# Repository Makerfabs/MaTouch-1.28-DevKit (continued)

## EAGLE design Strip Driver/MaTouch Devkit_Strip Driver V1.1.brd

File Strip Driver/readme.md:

# MaTouch1.28" DevKit Strip Driver

```c++
/*
Library version:
Arduino IDE 2.3.4
esp32 V3.1.1
GFX Library for Arduino v1.5.4
lvgl v8.3.11
RTClib v2.1.4
Adafruit BusIO v1.16.2
ESP32Time v2.0.6

Tools:
USB CDC On Boot: Enabled
Flash size: 16MB(128Mb)
Partition Schrme: 16M Flash(3MB APP/9.9MB FATFS)
PSRAM: OPI PSRAM
*/
```
## Introduce

1.[How to use?](https://wiki.makerfabs.com/Matouch%201.28%20DevKit.html#23-rgb-led-strip-driver)

2.[How to upload code?](https://wiki.makerfabs.com/Matouch%201.28%20DevKit.html#33-rgb-led-strip-driver)

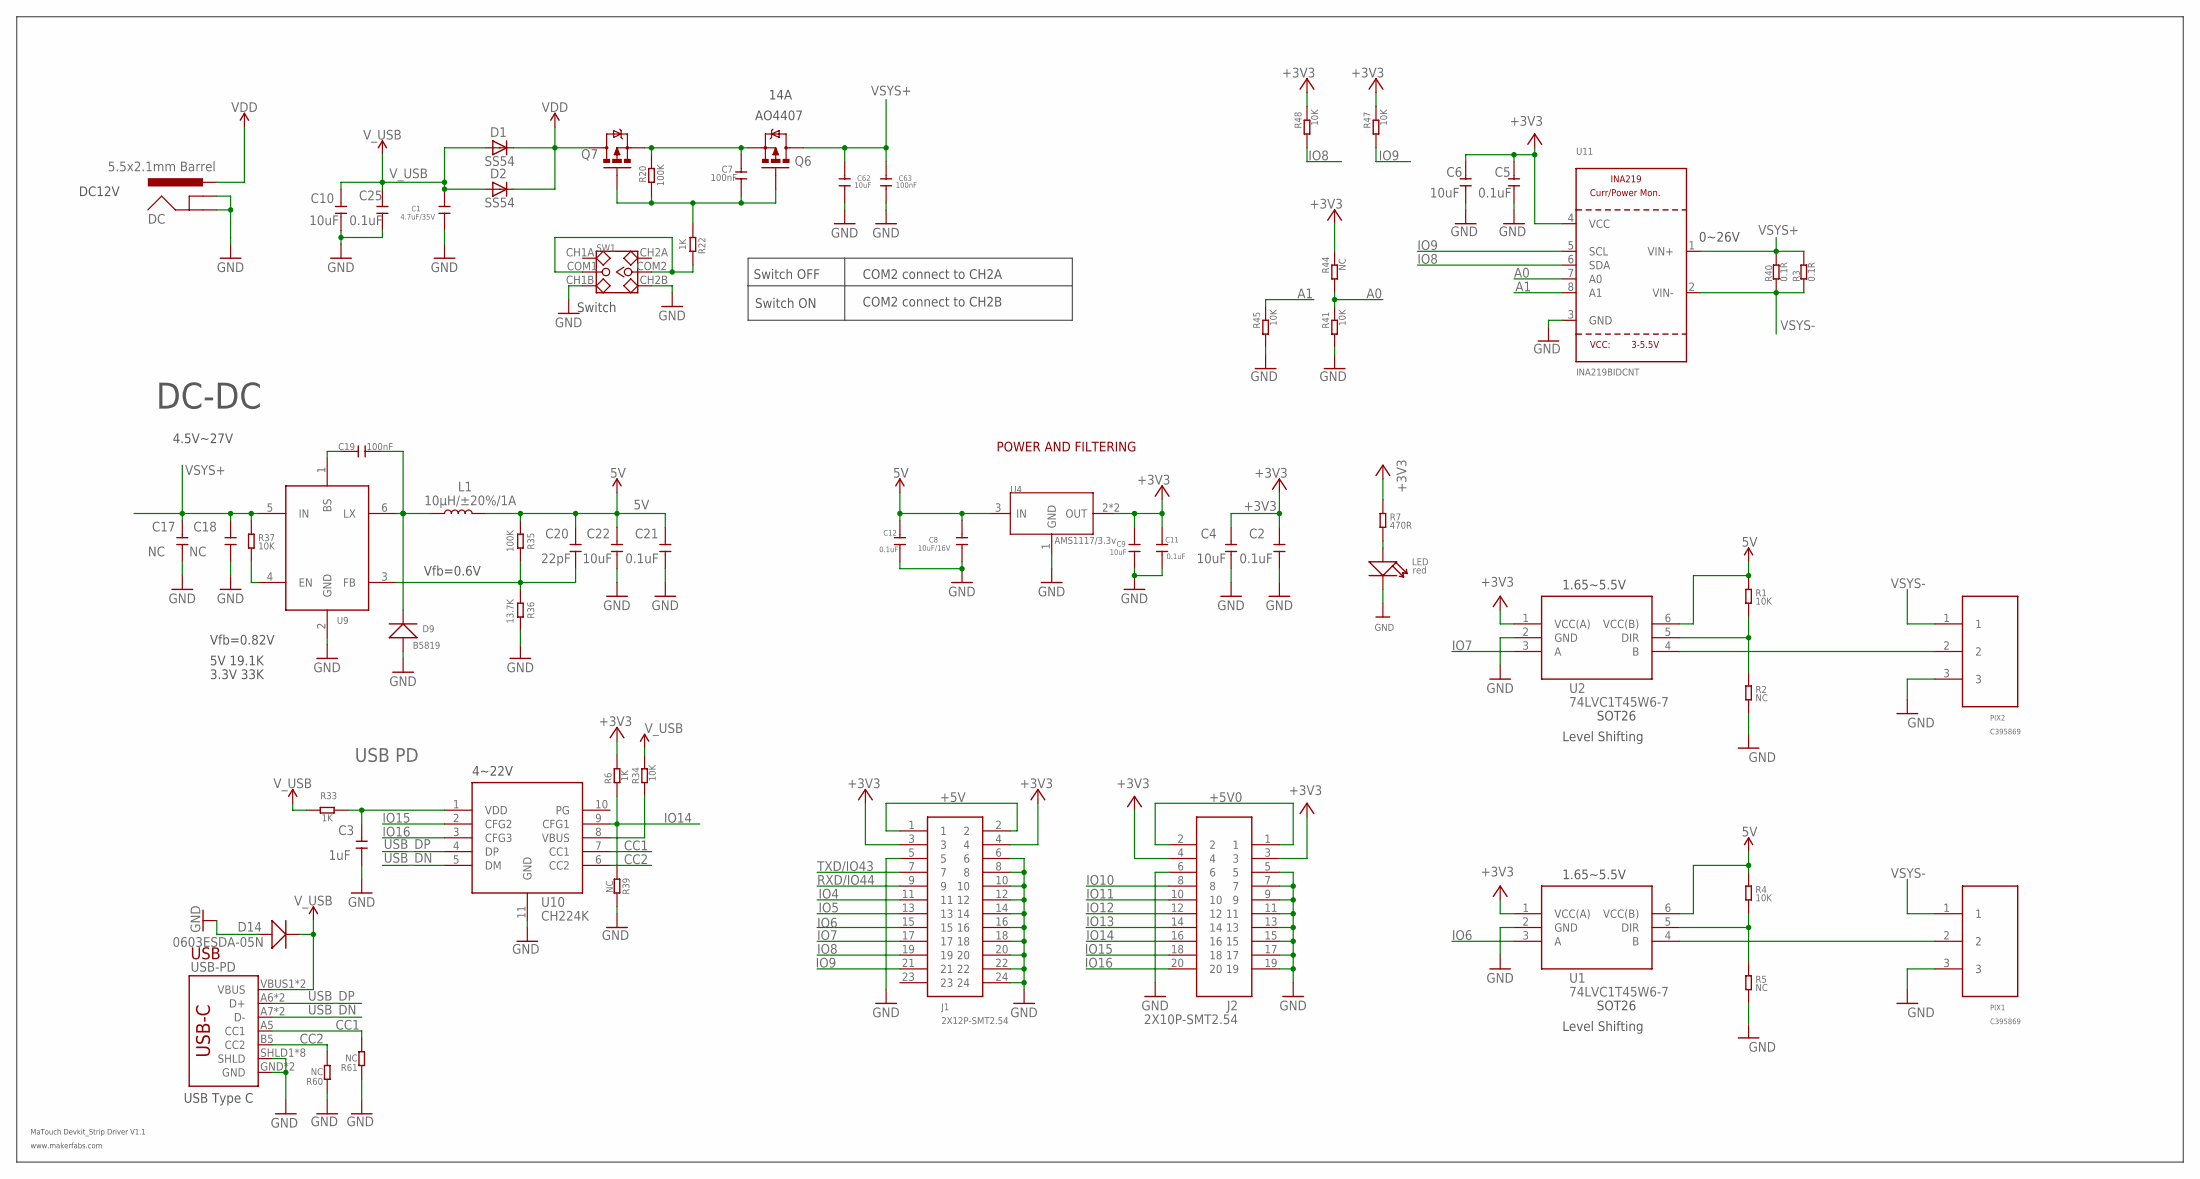
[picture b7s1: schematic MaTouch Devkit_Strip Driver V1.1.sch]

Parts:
C1: 4.7uF/35V; 0603
C2, C5, C11, C12, C21, C25: 0.1uF; 0603
C3: 1uF; 0603
C4, C6, C9, C10, C22, C62: 10uF; 0603
C7, C19, C63: 100nF; 0603
C8: 10uF/16V; 0603
C17, C18: NC; 0603
C20: 22pF; 0603
D1, D2: SS54; DO-214AC
D9: B5819; SOD123
D14: 0603ESDA-05N; DISCRETE_SOD523
DC: 5.5x2.1mm Barrel; POWER_JACK_SMD
J1: 2X12P-SMT2.54
J2: 2X10P-SMT2.54
L1: 10µH/±20%/1A; SRN6045
LED: red; DISCRETE_LED-0603
PIX1, PIX2: C395869; PIN_3P
Q6, Q7: MOSFET-PCHANNELFDS6675; SO08
R1, R4, R34, R37, R41, R45, R47, R48: 10K; R0603
R2, R5, R39, R44: NC; R0603
R3, R40: 0.1R; DISCRETE_R2512
R6, R22, R33: 1K; R0603
R7: 470R; R0603
R20, R35: 100K; R0603
R36: 13.7K; R0603
R60, R61: NC; DISCRETE_R0603
SW1: SWITCH-2CH-6P'90D'; 6P-2CH-2.54-9.0X3.6-90D
U1, U2: 74LVC1T45W6-7; SOT-23-6
U4: AMS1117/3.3v; SOT89
U9: SY8201ABC; SOT-23-6
U10: CH224K; ESSOP-10-150MIL
U11: INA219BIDCNT; SOT23-8
USB-PD: USB_C5; USB-C-16P-5

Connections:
5V: C8.1, C12.2, C20.2, C21.2, C22.2, L1.2, R1.1, R4.1, R35.1, U1.6 (VCC(B)), U2.6 (VCC(B)), U4.3 (IN)
+3V3: C2.2, C4.2, C5.2, C6.2, C9.1, C11.2, J1.3, J1.4, J2.3, J2.4, R6.2, R7.1, R44.2, R47.2, R48.2, U1.1 (VCC(A)), U2.1 (VCC(A)), U4.2 (OUT), U4.4 (OUT), U11.4 (VCC)
+5V: J1.1, J1.2
+5V0: J2.1, J2.2
A0: R41.2, R44.1, U11.7 (A0)
A1: R45.2, U11.8 (A1)
CC1: R61.2, U10.7 (CC1), USB-PD.A5 (CC1)
CC2: R60.2, U10.6 (CC2), USB-PD.B5 (CC2)
GND: C1.2, C2.1, C3.1, C4.1, C5.1, C6.1, C8.2, C9.2, C10.1, C11.1, C12.1, C17.1, C18.1, C21.1, C22.1, C25.1, C62.1, C63.1, D9.+, D14.+, DC.GND (GNDBREAK), DC.P$4 (GND), J1.5, J1.6, J1.8, J1.10, J1.12, J1.14, J1.16, J1.18, J1.20, J1.22, J1.24, J2.5, J2.6, J2.7, J2.9, J2.11, J2.13, J2.15, J2.17, J2.19, LED.-, PIX1.3, PIX2.3, R2.2, R5.2, R36.2, R39.2, R41.1, R45.1, R60.1, R61.1, SW1.CH1B, SW1.CH2B, U1.2 (GND), U2.2 (GND), U4.1 (GND), U9.2 (GND), U10.11 (GND), U11.3 (GND), USB-PD.GND, USB-PD.GND2 (GND), USB-PD.SHLD1 (SHLD), USB-PD.SHLD2 (SHLD), USB-PD.SHLD3 (SHLD), USB-PD.SHLD4 (SHLD), USB-PD.SHLD5 (SHLD), USB-PD.SHLD6 (SHLD), USB-PD.SHLD7 (SHLD), USB-PD.SHLD8 (SHLD)
IO4: J1.11
IO5: J1.13
IO6: J1.15, U1.3 (A)
IO7: J1.17, U2.3 (A)
IO8: J1.19, R48.1, U11.6 (SDA)
IO9: J1.21, R47.1, U11.5 (SCL)
IO10: J2.8
IO11: J2.10
IO12: J2.12
IO13: J2.14
IO14: J2.16, R6.1, R39.1, U10.9 (CFG1)
IO15: J2.18, U10.2 (CFG2)
IO16: J2.20, U10.3 (CFG3)
unnamed: R4.2, R5.1, U1.5 (DIR)
unnamed: PIX2.2, U2.4 (B)
unnamed: PIX1.2, U1.4 (B)
unnamed: LED.+, R7.2
unnamed: C7.1, Q6.4 (G), Q7.4 (G), R20.2, R22.2
unnamed: R22.1, SW1.COM1, SW1.COM2
unnamed: C19.2, D9.-, L1.1, U9.6 (LX)
unnamed: C19.1, U9.1 (BS)
unnamed: C20.1, R35.2, R36.1, U9.3 (FB)
unnamed: R37.2, U9.4 (EN)
unnamed: C3.2, R33.2, U10.1 (VDD)
unnamed: R34.1, U10.8 (VBUS)
unnamed: C7.2, Q6.1 (S), Q6.2 (S), Q6.3 (S), Q7.1 (S), Q7.2 (S), Q7.3 (S), R20.1
unnamed: R1.2, R2.1, U2.5 (DIR)
RXD/IO44: J1.9
TXD/IO43: J1.7
USB_DN: U10.5 (DM), USB-PD.A7 (D-), USB-PD.B7 (D-)
USB_DP: U10.4 (DP), USB-PD.A6 (D+), USB-PD.B6 (D+)
VDD: D1.C, D2.C, DC.VIN0 (PWR), Q7.5 (D), Q7.6 (D), Q7.7 (D), Q7.8 (D)
VSYS+: C17.2, C18.2, C62.2, C63.2, Q6.5 (D), Q6.6 (D), Q6.7 (D), Q6.8 (D), R3.2, R37.1, R40.2, U9.5 (IN), U11.1 (VIN+)
VSYS-: PIX1.1, PIX2.1, R3.1, R40.1, U11.2 (VIN-)
V_USB: C1.1, C10.2, C25.2, D1.A, D2.A, D14.-, R33.1, R34.2, USB-PD.VBUS1 (VBUS), USB-PD.VBUS2 (VBUS)

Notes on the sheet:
MaTouch Devkit_Strip Driver V1.1
www.makerfabs.com
Level Shifting
SOT26
1.65~5.5V
DC-DC
Switch OFF
Switch ON
COM2 connect to CH2A
COM2 connect to CH2B
Vfb=0.6V
4.5V~27V
USB PD
4~22V
USB
USB Type C
0~26V
DC12V
AO4407
14A
Switch
POWER AND FILTERING
Vfb=0.82V
5V 19.1K
3.3V 33K

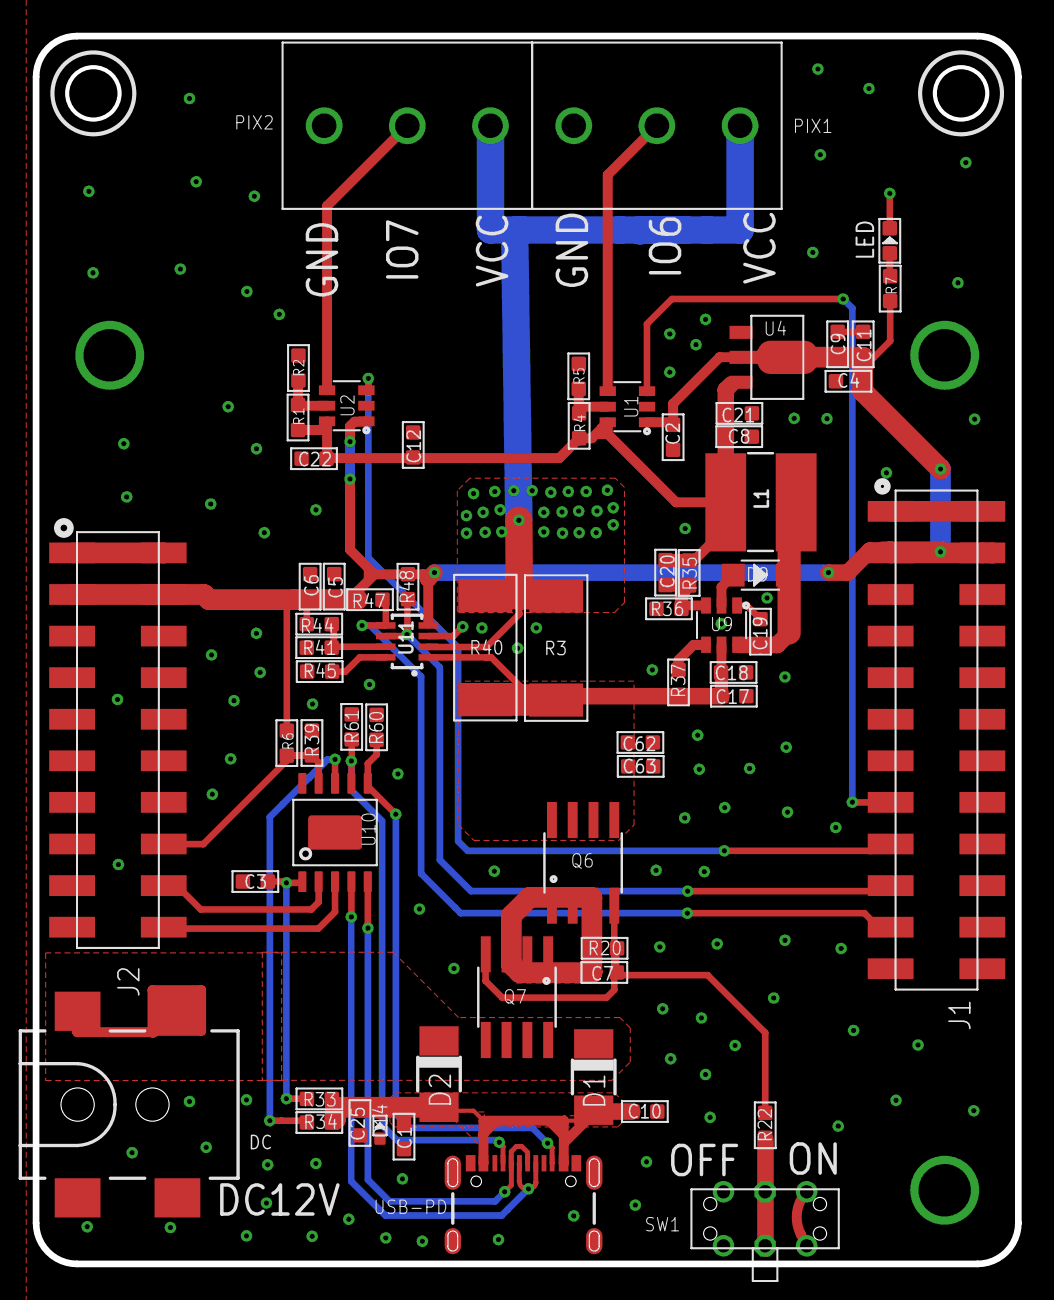
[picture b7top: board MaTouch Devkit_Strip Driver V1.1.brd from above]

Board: 2 copper layers, 60.0 x 75.0 mm, 66 parts (1 on the bottom side), 36 nets.

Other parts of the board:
U$2: MAKERFABS_0.3

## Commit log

2024-09-26 Create project
2024-09-26 Upload hardware
2024-09-27 change dictory
2025-01-07 Add Code
2025-01-20 Add project
2025-02-12 Update library version
2025-02-13 Add on/off function
2025-02-14 Updata readme.md
2025-02-17 Correct the wrong word
2025-02-18 增加硬件pdf文件
2025-02-19 Add text display
2025-02-19 Update LED_Screen.ino
    增加了软件版本管理
2025-02-19 Update LED_Screen.ino
    撤回刚刚的提交(增加版本管理)
2025-02-19 Update LED_Screen.ino
    1.添加代码注释
    2.添加版本管理日志
2025-02-20 Update LED_Screen.ino
    V1.0.2版本
    1.添加事件组
    2.将encoder_func函数添加到中断
2025-02-20 Update LED_Screen.ino
    v1.0.3
    规范提交的版本信息
2025-02-21 Upload code
    1.删除全开，全关按键
    2.修改ui，增大了按键，文字等显示
    3.添加了部分注释
2025-02-21 Update code
    1.添加开机界面
2025-02-24 Update
    1.修改返回按键ui
2025-02-24 增加英文注释
2025-02-24 修改版本管理
2025-02-25 Update library version
    更新成最新版本V1.5.4
2025-02-25 Update Step_Motor.ino
    1.添加版本管理注释
    2.修改速度单位
2025-02-25 Update DC_Driver.ino
    1.添加版本管理注释
2025-02-25 Add readme
2025-02-26 Update ui
    1.全关按钮改成全开+全关
    2.数量由60改成300
    4.模式页面添加mode标签
2025-02-26 Update
    1.修改屏幕切换问题
2025-02-27 Update RGB_LED_Strip.ino
    1.亮度添加开关功能
2025-02-27 Update
    添加灯带数量至300个
2025-02-27 Update RGB_LED_Strip.ino
    1.0.4版本，优化流水灯功能
2025-02-28 1.0.5版本，优化流水灯功能
2025-02-28 Update RGB_LED_Strip.ino
    1.修改低亮度不闪烁bug
    2.修改数量改变后灯不灭bug
2025-02-28 Update ui
    1.修改流水灯正反向的描述
    2.添加显示电流label
    3.修改部分字体大小
2025-02-28 Update
    添加电流检测功能
2025-02-28 Update hardware
2025-03-11 Add clock project
2025-03-19 Update hardware file
2025-03-19 Add hardware file
2025-03-19 Update Relay_8_Channel.ino
    Modify to English Notes
2025-03-19 Update ui.h
    Modify to English Notes
2025-05-22 Add video code
2025-07-04 Add demo
2025-07-21 Add ui design demo
2025-12-23 add esp-idf example
